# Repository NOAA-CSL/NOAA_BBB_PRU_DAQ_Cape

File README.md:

# NOAA BeagleBone Black (BBB) PRU DAQ Cape

<p>The NOAA BeagleBone Black PRU and DAQ Cape was developed for the NOAA Printed Optical Particle 
Spectrometer (POPS) instrument that is used to make balloon and aircraft particle concentration measurements. The 
POPS instrument is patented and can be licensed for $500 per year.  Contact Derek Parks (Derek.Parks@NOAA.gov) for 
more information. This cape and software has been patented and is being presented (with the included disclaimer) 
free for public download, modification and use. The programs that are presented are for the POPS instrument, and are
meant as an example and guide for developing other applications.

Cape Features
-----------------

* A high-speed LVDT serial interface using a DS90C124 deserializer.  It connects via a SATA cable to an 
LT2203 16 bit A/D converter located on the photomultiplier (PMT) interface board, sampling at 4 MHz.
This uses both PRUs to implement, and the data is passed in memory.

* MAX5802 D/A converter providing two 12-bit analog out channels (0-5 V) used for controlling the 
instrument's flow rate and laser power (0-5 V).

* An on-board MS5607-02BA03 pressure/temperature sensor.

* A DS3231 hardware realtime clock and battery holder.

* MAX3223 RS232 interface for two UARTs. UART1 is duplicated in TTL.

* M24256 cape EEPROM.

Provided Information
------------------------

* This README.md.

* SOFTWARE DISCLAIMER.md:  This file is to be included with any code that is copied from this 
distribution and used in another application.

* NOAA_BBB_PRU_DAQ_Cape_Setup.md:  This file describes how to setup the BeagleBone Black to 
correctly configure it to work with the cape.

* NOAA_BBB_PRU_DAQ_Cape Pin Use.md:  The pins used by the cape, and other pin information, is 
presented in this document as a table.

Hardware
------------

* README.md file for the hardware.

* NOAA_BBB_PRU_DAQ_Cape, PMT interface board, and base plate Eagle PCB files.

* BOM as an Excel spreadsheet for the boards.

Software and Examples
-------------------------

* build and build_dt:  Scripts to build the *.c and *.p files provided.

* cape-bone-iio-00A0.dtbo:  The analog in device tree binary object file.

* clock_init.sh:  The clock initialization shell.

* iolib.c, iolib.h, iolib.o, libiofunc.a and MAKEFILE:  The library libio is used for digital IO in the software.
	
* NOAA *.dts and *.dtbo files:  Used to set the Analog In, GPIO, PRUs and UARTS pins.

* PRU0_ParData.p, PRU1_All.p and PRU1_All_dt.p: Assembly language programs for the POPS instrument.

* POPS_BBB.c:  The main program for the POPS instrument. Demonstrates the capacity of the cape.

* POPS_BBB.cfg:  The configuration file for the POPS instrument.

* rc.local:  File for startup of services on boot.

* rtc-ds1307.service:  Hardware realtime clock service setup.

* Software_install_1 and Software_install_2:  Scripts for installing the software on the 
Beaglebone Black.

Disclaimer
----------------------------------

This repository is a scientific product and is not official communication of the National Oceanic and Atmospheric 
Administration, or the United States Department of Commerce. All NOAA GitHub project code is provided on an ‘as is’ basis 
and the user assumes responsibility for its use. NOAA has relinquished control of the information and no longer has 
responsibility to protect the integrity, confidentiality, or availability of the information. Any claims against the Department 
of Commerce or Department of Commerce bureaus stemming from the use of this GitHub project will be governed by all applicable 
Federal law. Any reference to specific commercial products, processes, or services by service mark, trademark, manufacturer,
or otherwise, does not constitute or imply their endorsement, recommendation or favoring by the Department of Commerce. The 
Department of Commerce seal and logo, or the seal and logo of a DOC bureau, shall not be used in any manner to imply endorsement 
of any commercial product or activity by DOC or the United States Government.

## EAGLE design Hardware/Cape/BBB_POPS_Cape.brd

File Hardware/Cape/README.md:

Beagle Bone Black (BBB) POPS Cape Notes
=======================================

<p>This cape is intended to be a part of a stack of printed circuit boards that comprise 
of the POPS instrument.  As you might expect, the cape plugs into the BBB and has M-F 
pass through connectors.  As currently used, the cape then plugs into a ‘base plate’ that
has some signal conditioning, and the rest of the instrument attaches to the base plate.  
Some signals are passed via the usual P8-P9 connectors, while other signals are passed to
the base plate via JP1, a 14 pin connector of similar style as P8 and P9.  If a base 
plate is not to be used, these signals are broken out on other connectors.

Note: The BeagelBone Black is mounted upside down on the base plate.

<p>The cape is powered by a signal labeled ‘V-Batt’.  This comes in via J1 pins 3 and 4,
or if a baseplate is not used, via the connector named ‘BATTERY_IN’.  This voltage is 
scaled and monitored via A/D channel AI6 pin P9.35.  To turn on the cape (which powers 
the BBB) the ‘ON’ button is pressed.  There is an ON button located on the cape, and can 
also have one on the baseplate using pin 12 of JP1.  The ON button turns on FET T3 which 
supplies +12V to the cape and to the base plate via J1 pins 5 and 6.  On the cape is a 5V 
regulator which then supplies +5V to the BBB via P9 pins P9.5 and P9.6.  The BBB then 
regulates the 5V down to +3.3V and supplies it back to the cape  via pins P9.3 and P9.4.  
Among other things, this 3.3V is then used to hold on FET T3 so the system remains powered 
up after the ON button is released.  When the BBB shuts down, 3.3V is removed from P9 and 
if the ON button is not pressed, power is removed from the rest of the system.

POPS Cape top view.

POPS Cape bottom view.

One of the functions of the cape is to read a differential pressure signal, compare against a setpoint (set by one of the two D/A channels) and control a small pump to maintain the setpoint.  The flow signal is the difference in pressure between the two ports on a laminar flow element.  This sub-system provides for a constant volume of gas flow.  The pump power is supplied via JP1 pins 1 and 2.  If a base plate is not used, connector P6 can be used.
The flow signal from the differential pressure sensor is supplied to the cape either via JP1 pin 13 or if the baseplate is not used, via J4.  It is scaled (conditioned) and is presented to the BBB via AIN0 P9.39.
Two 10K thermistors are measured on the POPS instrument.  One is external to the instrument connected to a connector on the base plate.  This in turn connects to the cape via JP1 pins 9 and 11.  This signal is scaled and provided to the BBB via AIN5 on P9.36.  The other thermistor monitors the laser diode temperature and connects to the POPS optical chamber via 5 pin P1 (note: not JP1!) pins 4 and 5.  Scaled signal is provided to the BBB via AIN2 on P9.367.  On both thermistors, one end is connected to a 3.6019V reference voltage and the other end connects to a 1.24K resistor to ground.  1.24K is also the resistance of the thermistor at its maximum expected temperature of 80.24 deg. C, which presents 1.8V to the BBB.  At 25 deg. C the thermistor value is 10K which presents 0.728V to the BBB.
The last signal on JP1 is named ‘PUSH_2_STOP’.  There is a button on the cape and can have a button on the baseplate.  This signal is buffered and presented to the BBB via P8.30.  It is monitored by the software and when asserted, (list the steps the software does, such as turn off laser, pump, stop taking data, close the files, run the shutdown sequence which removes the +3.3V signal from T3 and removes power to the BBB and cape).

Analog In Scale Factors.

AI0: Flow Signal.  5.036V from diff. pressure signal presents 1.8V to the BBB.
AI1: Pump Feedback.  15.000V from pump control circuit presents 1.8V to BBB.
AI2: Laser Temperature (10K Thermistor).  Max temperature is 80.24 deg. C which presents 1.8V to BBB.  25 deg. C presents 0.728V to BBB.
AI3: Laser Feedback. 5.036V from laser driver presents 1.8V to BBB.
AI4: Laser Photodiode Monitor. 5.036V from laser driver presents 1.8V to BBB.
AI5: External 10K Thermistor.  Max temperature is 80.24 deg. C which presents 1.8V to BBB.  25 deg. C presents 0.728V to BBB.
AI6: Battery Voltage. 20.119V input presents 1.8V to the BBB.

U1: I2C M24256 EEPROM. 

On this cape is a typical EEPROM which is not currently used with our software.  Solder jumpers SJ3 and SJ4 select the address.  By default (no solder jumpers) the address is 0x57.  0x54, 0x55, and 0x56 are the other options.  When SJ5 is shorted with a solder blob it write protects the EEPROM.  It is not write protected by default.  The SDA line is connected to P9.20 and the SCL line is connected to P9.19.

U2: I2C DS3231MZ/V Real Time Clock.

On this cape is a DS3231 battery backed up Real Time Clock.  This particular device has it’s own internal temperature compensated oscillator which keeps it accurate to +/- 5ppm (+/- 0.432 seconds per day) over it’s temperature range.  It’s fixed address is 0x68.  The SDA line is connected to P9.20 and the SCL line is connected to P9.19.  Backup power is provided by a BR1225 coin cell permanently soldered to the cape.  Not using a battery holder insures the coin cell won’t be jarred free.

U3: I2C MAX5802 12 bit dual D/A converter.

On this cape is a MAX5802 12 bit dual D/A converter.  It’s address is set to 0x0F by default and can be changed to 0x0C by moving solder jumper JMP7 to Vcc, or 0x0E by not connecting the solder jumper to either pad.  It is pin selected to have both outputs at 0V on power up and software selected max output voltage of 4.096V.  Ch. 1 controls the laser current and has a 0 to 100mA range.  The laser diode is rated for 100 mA continuous.  Out Ch. 2 provides the set point for the flow controller.  The controller servos the voltage to the pump so that this set point matches the signal from the flow sensor.  Since the actual flow signal is dependent on the laminar flow element geometries and particular differential pressure sensor used, the final calibration is done for each individual instrument.  Typical values have been around 3.5V from the D/A equal to 3 cc/second.

PRES1: SPI MS5607-02BA03 Barometric Pressure sensor with Temperature.

The MS5607 Barometric pressure sensor is used to measure altitude of the POPS instrument.  It has a range of 10 to 1200 mbar and a resolution of 0.024 mbar (20 cm of altitude).  Included is a 0.01 deg. C resolution, +/- 0.8 deg. C. accurate temperature sensor 
which is used to monitor the cape’s temperature.  The BBB talks to it via a bit-banged SPI interface with the SCLK to P9.13, the chip select signal connected to P9.14, the SDO to P9.15 and SDI to P9.16.

Serial Ports: RS-232 and TTL

There are two serial ports brought out on this cape.  UART1 TX signal (data leaving the cape) is on pin 9.24 and RX signal (data entering the cape) is on pin 9.26.  UART2 TX signal is on pin 9.21 and RX signal is on pin 9.22.  UART1 has two connectors.  J5 has the 3.3V TTL signals on it and J2 has the same data but buffered for RS-232 signal levels.  As for the UART1 RX signal, there is a solder jumper JMP2 that selects between the signal from the RS-232 buffer chip IC6 (MAX3223) or the signal from J5.  Since for our current applications no data is received on UART1 we currently don’t populate either side of solder jumper JMP2.  There is a through hole jumper connector that serves the same function as JMP2 called JP2.  If we had to frequently change which source of data JP2 would allow this without use of a soldering iron.  UART1 is used to send status data to either aircraft telemetry (the RS-232 buffered signal) or send 3.3V level status data to an IMET radiosonde via J5.  UART2 is always buffered to RS-232 signal levels and is on connector J3.  UART2 is used to communicate with a laptop running LabVIEW user interface software.

P2: High Speed A/D connector

In order to reduce interference and noise pickup, the high speed A/D converter is located as close to the signal source (Photo Multiplier Tube) as possible.  This converter is a Linear Technology LTC2203 16 bit, 25 MSPS converter with a parallel output, running at 4 MSPS.  The digital signals from the converter are serialized using a TI DS90C241 serializer.  The LVDS serial stream uses standard SATA connectors and cables to connect to the cape.  SATA cables were used for their low cost and availability.  Connector P2 on this cape has the serial data stream and provides power to the PMT and signal conditioning electronics.  The signals transferred are listed below.
Over/Underflow: P8.29
Data Ready: P8.27
AD15: P9.25
AD14: P9.41
AD13: P9.27
AD12: P9.42
AD11: P9.28
AD10: P9.30
AD9: P9.29
AD8: P9.31
AD7: P8.40
AD6:P9.39
AD5: P8.42
AD4: P8.41
AD3: P8.44
AD2: P8.43
AD1: P8.46
AD0: P8.45

There are 2 LEDs associated with the deserializer.  One to display the Over/Underflow status and another to show the status of the link between the deserializer and serializer.

P1: Laser connector

Connector P1 has 5 pins and connects to the laser inside the optical chamber.  Pin 1 is the laser diode Anode, pin 2 is the laser diode Cathode, and Pin 3 is the photodiode internal to the laser module.  0 to 100mA of current is controlled by the value on D/A channel A and the signal on pin 3 is signal conditioned and reported back to the BBB on channel AIN4.  Pin 4 has the reference voltage for the thermistor that is mounted on the laser’s heat sink, and pin 5 connects to ground through a 1.24K resistor.  The voltage on pin 5 is conditioned and sent to the BBB on channel AIN2.

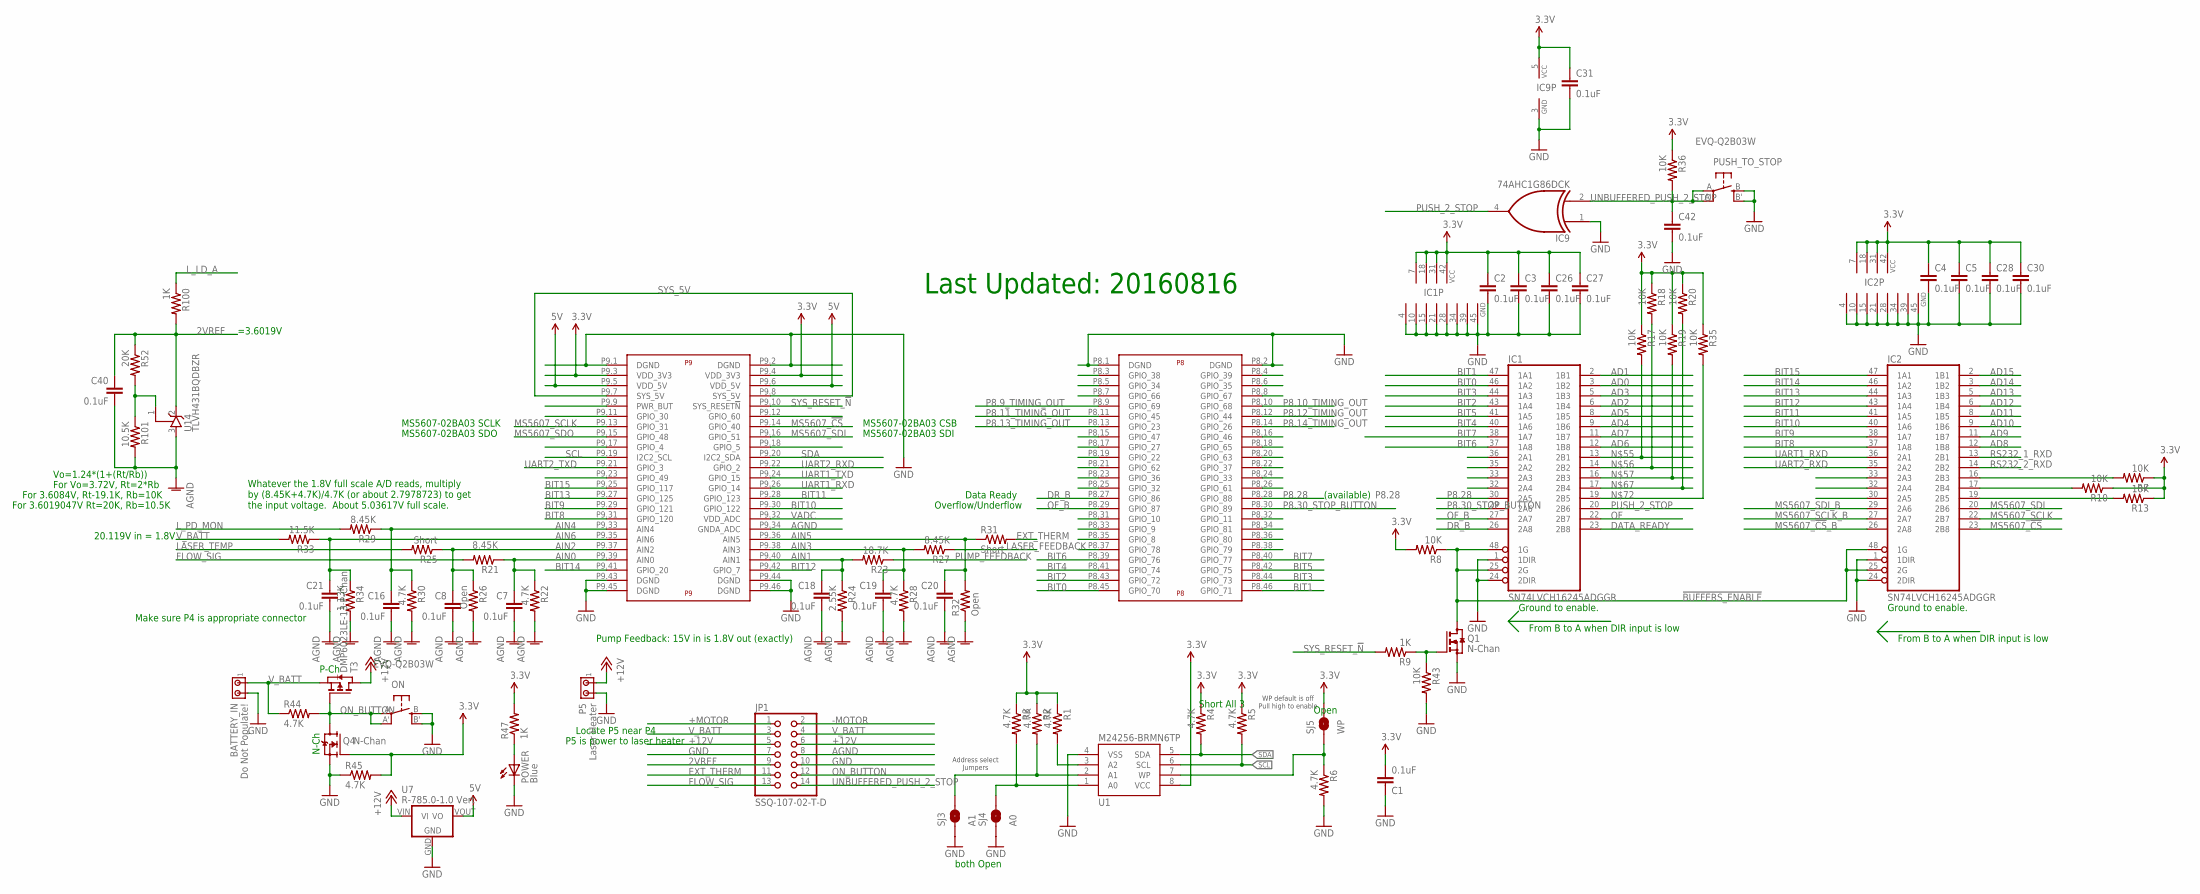
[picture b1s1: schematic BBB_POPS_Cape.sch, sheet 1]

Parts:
BATTERY_IN: Do Not Populate!; 070543-0036
C1, C2, C3, C4, C5, C7, C8, C16, C18, C19, C20, C21, C26, C27, C28, C30, C31, C40, C42: 0.1uF; 0603
IC1, IC2: SN74LVCH16245ADGGR; TSSOP-48
IC9: 74AHC1G86DCK; SC70-5
JP1: SSQ-107-02-T-D; 2X07_ROUND
ON: EVQ-Q2B03W; EVQ-Q2
P5: Laser Heater; 501568-0207_2-PIN
POWER: Blue; LED-805
PUSH_TO_STOP: EVQ-Q2B03W; EVQ-Q2
Q1: N-Chan; SOT23
Q4: N-Chan; SOT-23
R1, R2, R3, R4, R5, R6, R22, R28, R30, R44, R45: 4.7K; 0603
R7, R8, R10, R13, R17, R18, R19, R20, R35, R36, R43: 10K; 0603
R9, R47, R100: 1K; 0603
R21, R27, R29: 8.45K; 0603
R23: 18.7K; 0603
R24: 2.55K; 0603
R25, R31: Short; 0603
R26, R32: Open; 0603
R33: 11.5K; 0603
R34: 1.13K; 0603
R52: 20K; 0603
R101: 10.5K; 0603
SJ3: A1; SJ_2S-NO
SJ4: A0; SJ_2S-NO
SJ5: WP; SJ_2S-NO
T3: DMP6023LE-13 P-Chan; SOT223
U1: M24256-BRMN6TP; SO08
U7: R-785.0-1.0 Vert; RECOM_R-78X-1.0
U14: TLVH431BQDBZR; SOT23
U$2: BEAGLE_BONE_BLACK_CAPEME; MY_BBB_CAPE

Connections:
2VREF: C40.1, JP1.9, R52.1, R100.2, U14.2 (C); also elsewhere on the board
3.3V: C1.2, C2.1, C3.1, C4.1, C5.1, C26.1, C27.1, C28.1, C30.1, C31.1, IC1.7 (VCC), IC1.18 (VCC), IC1.31 (VCC), IC1.42 (VCC), IC2.7 (VCC), IC2.18 (VCC), IC2.31 (VCC), IC2.42 (VCC), IC9.5 (VCC), Q4.1 (G), R1.1, R2.1, R3.1, R4.1, R5.1, R7.1, R8.2, R10.1, R13.1, R17.1, R18.1, R19.1, R20.1, R35.1, R36.1, R45.2, R47.2, SJ5.2, U1.8 (VCC), U$2.P9.3 (VDD_3V3), U$2.P9.4 (VDD_3V3); also elsewhere on the board
5V: U7.VOUT (VO), U$2.P9.5 (VDD_5V), U$2.P9.6 (VDD_5V); also elsewhere on the board
!BUFFERS_ENABLE: IC1.25 (2G), IC1.48 (1G), IC2.25 (2G), IC2.48 (1G), Q1.3 (D), R8.1
+12V: JP1.5, JP1.6, P5.1, T3.2 (D), T3.4 (D), U7.VIN (VI); also elsewhere on the board
+MOTOR: JP1.1; also elsewhere on the board
-MOTOR: JP1.2; also elsewhere on the board
A0: R3.2, SJ4.2, U1.1 (A0)
A1: R2.2, SJ3.2, U1.2 (A1)
AD0: IC1.3 (1B2); also elsewhere on the board
AD1: IC1.2 (1B1); also elsewhere on the board
AD2: IC1.6 (1B4); also elsewhere on the board
AD3: IC1.5 (1B3); also elsewhere on the board
AD4: IC1.9 (1B6); also elsewhere on the board
AD5: IC1.8 (1B5); also elsewhere on the board
AD6: IC1.12 (1B8); also elsewhere on the board
AD7: IC1.11 (1B7); also elsewhere on the board
AD8: IC2.12 (1B8); also elsewhere on the board
AD9: IC2.11 (1B7); also elsewhere on the board
AD10: IC2.9 (1B6); also elsewhere on the board
AD11: IC2.8 (1B5); also elsewhere on the board
AD12: IC2.6 (1B4); also elsewhere on the board
AD13: IC2.5 (1B3); also elsewhere on the board
AD14: IC2.3 (1B2); also elsewhere on the board
AD15: IC2.2 (1B1); also elsewhere on the board
AGND: C7.2, C8.2, C16.2, C18.2, C19.2, C20.2, C21.2, C40.2, JP1.8, R22.2, R24.2, R26.2, R28.2, R30.2, R32.1, R34.2, R101.2, U14.3 (A), U$2.P9.34 (GNDA_ADC); also elsewhere on the board
AIN0: C7.1, R21.1, R22.1, U$2.P9.39 (AIN0)
AIN1: C18.1, R23.2, R24.1, U$2.P9.40 (AIN1)
AIN2: C8.1, R25.1, R26.1, U$2.P9.37 (AIN2)
AIN3: C19.1, R27.2, R28.1, U$2.P9.38 (AIN3)
AIN4: C16.1, R29.1, R30.1, U$2.P9.33 (AIN4)
AIN5: C20.1, R31.1, R32.2, U$2.P9.36 (AIN5)
AIN6: C21.1, R33.1, R34.1, U$2.P9.35 (AIN6)
BIT0: IC1.46 (1A2), U$2.P8.45 (GPIO_70)
BIT1: IC1.47 (1A1), U$2.P8.46 (GPIO_71)
BIT2: IC1.43 (1A4), U$2.P8.43 (GPIO_72)
BIT3: IC1.44 (1A3), U$2.P8.44 (GPIO_73)
BIT4: IC1.40 (1A6), U$2.P8.41 (GPIO_74)
BIT5: IC1.41 (1A5), U$2.P8.42 (GPIO_75)
BIT6: IC1.37 (1A8), U$2.P8.39 (GPIO_76)
BIT7: IC1.38 (1A7), U$2.P8.40 (GPIO_77)
BIT8: IC2.37 (1A8), U$2.P9.31 (GPIO_120)
BIT9: IC2.38 (1A7), U$2.P9.29 (GPIO_121)
BIT10: IC2.40 (1A6), U$2.P9.30 (GPIO_122)
BIT11: IC2.41 (1A5), U$2.P9.28 (GPIO_123)
BIT12: IC2.43 (1A4), U$2.P9.42 (GPIO_7)
BIT13: IC2.44 (1A3), U$2.P9.27 (GPIO_125)
BIT14: IC2.46 (1A2), U$2.P9.41 (GPIO_20)
BIT15: IC2.47 (1A1), U$2.P9.25 (GPIO_117)
DATA_READY: IC1.23 (2B8); also elsewhere on the board
DR_B: IC1.26 (2A8), U$2.P8.27 (GPIO_86)
EXT_THERM: JP1.11, R31.2; also elsewhere on the board
FLOW_SIG: JP1.13, R21.2; also elsewhere on the board
GND: BATTERY_IN.P$2 (2), C1.1, C2.2, C3.2, C4.2, C5.2, C26.2, C27.2, C28.2, C30.2, C31.2, C42.2, IC1.1 (1DIR), IC1.4 (GND), IC1.10 (GND), IC1.15 (GND), IC1.21 (GND), IC1.24 (2DIR), IC1.28 (GND), IC1.34 (GND), IC1.39 (GND), IC1.45 (GND), IC2.1 (1DIR), IC2.4 (GND), IC2.10 (GND), IC2.15 (GND), IC2.21 (GND), IC2.24 (2DIR), IC2.28 (GND), IC2.34 (GND), IC2.39 (GND), IC2.45 (GND), IC9.1 (I0), IC9.3 (GND), JP1.7, JP1.10, ON.B (S), ON.B' (S1), P5.2, POWER.C, PUSH_TO_STOP.B (S), PUSH_TO_STOP.B' (S1), Q1.2 (S), Q4.2 (S), R6.2, R43.2, R45.1, SJ3.1, SJ4.1, U1.4 (VSS), U7.GND, U$2.P8.1 (DGND), U$2.P8.2 (DGND), U$2.P9.1 (DGND), U$2.P9.2 (DGND), U$2.P9.43 (DGND), U$2.P9.44 (DGND), U$2.P9.45 (DGND), U$2.P9.46 (DGND); also elsewhere on the board
LASER_FEEDBACK: R27.1; also elsewhere on the board
LASER_TEMP: R25.2; also elsewhere on the board
L_LD_A: R100.1; also elsewhere on the board
L_PD_MON: R29.2; also elsewhere on the board
MS5607_!CS: IC2.23 (2B8), U$2.P9.14 (GPIO_40)
MS5607_!CS!_B: IC2.26 (2A8); also elsewhere on the board
MS5607_SCLK: IC2.22 (2B7), U$2.P9.13 (GPIO_31)
MS5607_SCLK_B: IC2.27 (2A7); also elsewhere on the board
MS5607_SDI: IC2.20 (2B6), U$2.P9.16 (GPIO_51)
MS5607_SDI_B: IC2.29 (2A6); also elsewhere on the board
MS5607_SDO: U$2.P9.15 (GPIO_48); also elsewhere on the board
unnamed: R6.1, SJ5.1, U1.7 (WP)
unnamed: Q1.1 (G), R9.1, R43.1
unnamed: IC2.16 (2B3), R7.2
unnamed: R1.2, U1.3 (A2)
unnamed: R52.2, R101.1, U14.1 (R)
unnamed: IC2.17 (2B4), R10.2
unnamed: IC2.19 (2B5), R13.2
unnamed: IC1.13 (2B1), R17.2
unnamed: IC1.14 (2B2), R18.2
unnamed: IC1.16 (2B3), R19.2
unnamed: IC1.17 (2B4), R20.2
unnamed: IC1.19 (2B5), R35.2
unnamed: POWER.A, R47.1
OF: IC1.22 (2B7); also elsewhere on the board
OF_B: IC1.27 (2A7), U$2.P8.29 (GPIO_87)
ON_BUTTON: JP1.12, ON.A, ON.A' (P1), Q4.3 (D), R44.2, T3.1 (G)
P8.9_TIMING_OUT: U$2.P8.9 (GPIO_69)
P8.10_TIMING_OUT: U$2.P8.10 (GPIO_68)
P8.11_TIMING_OUT: U$2.P8.11 (GPIO_45)
P8.12_TIMING_OUT: U$2.P8.12 (GPIO_44)
P8.13_TIMING_OUT: U$2.P8.13 (GPIO_23)
P8.14_TIMING_OUT: U$2.P8.14 (GPIO_26)
P8.28: IC1.30 (2A5), U$2.P8.28 (GPIO_88)
P8.30_STOP_BUTTON: IC1.29 (2A6), U$2.P8.30 (GPIO_89)
PUMP_FEEDBACK: R23.1; also elsewhere on the board
PUSH_2_STOP: IC1.20 (2B6), IC9.4 (O)
RS232_1_RXD: IC2.13 (2B1); also elsewhere on the board
RS232_2_RXD: IC2.14 (2B2); also elsewhere on the board
SCL: R5.2, U1.6 (SCL), U$2.P9.19 (I2C2_SCL); also elsewhere on the board
SDA: R4.2, U1.5 (SDA), U$2.P9.20 (I2C2_SDA); also elsewhere on the board
SYS_5V: U$2.P9.7 (SYS_5V), U$2.P9.8 (SYS_5V)
SYS_RESET_!N: R9.2, U$2.P9.10 (SYS_RESET!N)
UART1_RXD: IC2.36 (2A1), U$2.P9.26 (GPIO_14)
UART1_TXD: U$2.P9.24 (GPIO_15); also elsewhere on the board
UART2_RXD: IC2.35 (2A2), U$2.P9.22 (GPIO_2)
UART2_TXD: U$2.P9.21 (GPIO_3); also elsewhere on the board
UNBUFFERED_PUSH_2_STOP: C42.1, IC9.2 (I1), JP1.14, PUSH_TO_STOP.A, PUSH_TO_STOP.A' (P1), R36.2
VADC: U$2.P9.32 (VDD_ADC)
V_BATT: BATTERY_IN.P$1 (1), JP1.3, JP1.4, R33.2, R44.1, T3.3 (S)

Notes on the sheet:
WP default is off Pull high to enable
Address select Jumpers
Ground to enable.
(available)
Data Ready
Overflow/Underflow
Last Updated: 20160816
Open
both Open
Short All 3
Whatever the 1.8V full scale A/D reads, multiply by (8.45K+4.7K)/4.7K (or about 2.7978723) to get the input voltage. About 5.03617V full scale.
MS5607-02BA03 CSB
MS5607-02BA03 SCLK
MS5607-02BA03 SDO
MS5607-02BA03 SDI
Make sure P4 is appropriate connector
20.119V in = 1.8V
P5 is power to laser heater
Locate P5 near P4
From B to A when DIR input is low
Vo=1.24*(1+(Rt/Rb))
For Vo=3.72V, Rt=2*Rb
N-Ch
P-Ch
For 3.6084V, Rt-19.1K, Rb=10K
=3.6019V
For 3.6019047V Rt=20K, Rb=10.5K
Pump Feedback: 15V in is 1.8V out (exactly)

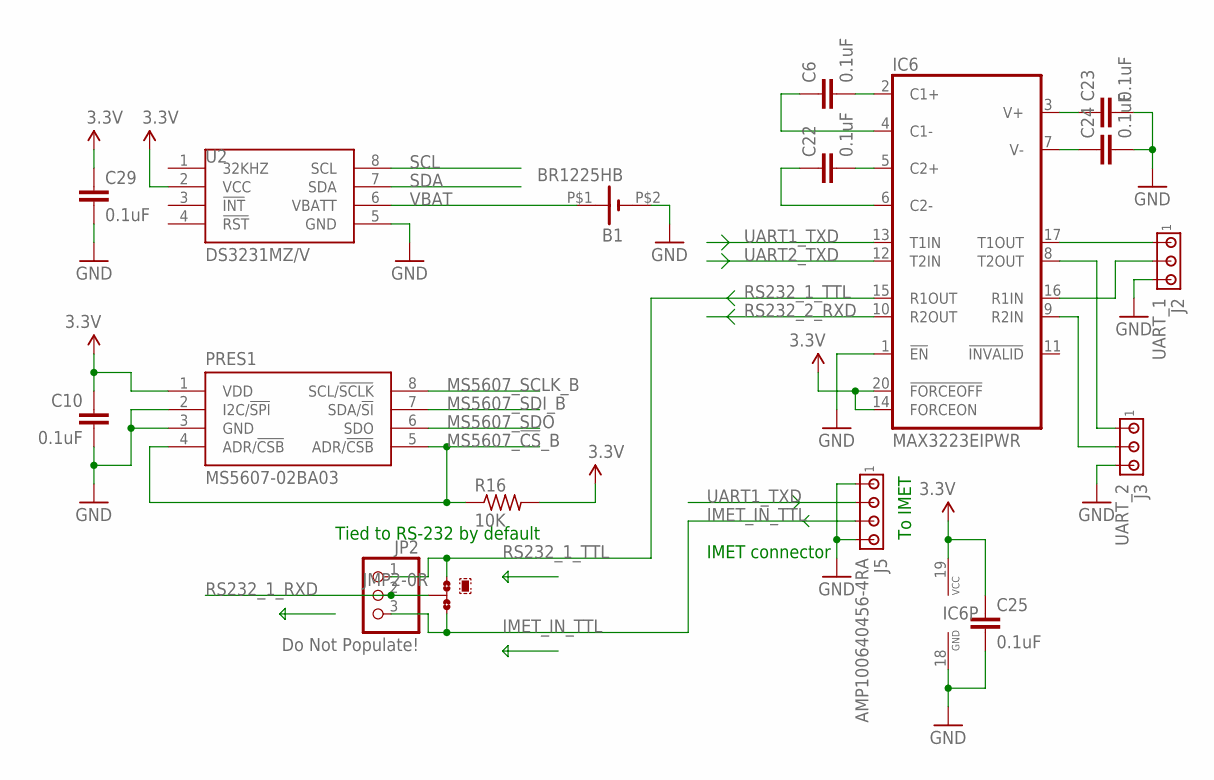
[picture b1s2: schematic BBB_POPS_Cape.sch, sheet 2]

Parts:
B1: BR1225HB; BR1225A/HB
C6, C10, C22, C23, C24, C25, C29: 0.1uF; 0603
IC6: MAX3223EIPWR; TSSOP20
J2: UART_1; 640457-3
J3: UART_2; 640457-3
J5: AMP100640456-4RA; 640457-4
JMP2: 0R-JUMPMINE; MY_C0R-JMP
JP2: Do Not Populate!; 1X03_ROUND
PRES1: MS5607-02BA03; MS5607-02BA
R16: 10K; 0603
U2: DS3231MZ/V; SO08

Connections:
3.3V: C10.1, C25.1, C29.1, IC6.14 (FORCEON), IC6.19 (VCC), IC6.20 (!FORCEOFF), PRES1.1 (VDD), R16.2, U2.2 (VCC); also elsewhere on the board
GND: B1.P$2 (-), C10.2, C23.2, C24.2, C25.2, C29.2, IC6.1 (!EN), IC6.18 (GND), J2.3, J3.3, J5.1, J5.4, PRES1.2 (I2C/!SPI), PRES1.3 (GND), U2.5 (GND); also elsewhere on the board
IMET_IN_TTL: J5.3, JMP2.3, JP2.3
MS5607_!CS!_B: PRES1.4 (ADR/!CSB), PRES1.5 (ADR/!CSB), R16.1; also elsewhere on the board
MS5607_SCLK_B: PRES1.8 (SCL/!SCLK); also elsewhere on the board
MS5607_SDI_B: PRES1.7 (SDA/!SI); also elsewhere on the board
MS5607_SDO: PRES1.6 (SDO); also elsewhere on the board
unnamed: IC6.16 (R1IN), J2.2
unnamed: IC6.8 (T2OUT), J3.1
unnamed: IC6.9 (R2IN), J3.2
unnamed: IC6.17 (T1OUT), J2.1
unnamed: C6.2, IC6.2 (C1+)
unnamed: C22.2, IC6.5 (C2+)
unnamed: C23.1, IC6.3 (V+)
unnamed: C24.1, IC6.7 (V-)
unnamed: C6.1, IC6.4 (C1-)
unnamed: C22.1, IC6.6 (C2-)
RS232_1_RXD: JMP2.2, JP2.2; also elsewhere on the board
RS232_1_TTL: IC6.15 (R1OUT), JMP2.1, JP2.1
RS232_2_RXD: IC6.10 (R2OUT); also elsewhere on the board
SCL: U2.8 (SCL); also elsewhere on the board
SDA: U2.7 (SDA); also elsewhere on the board
UART1_TXD: IC6.13 (T1IN), J5.2; also elsewhere on the board
UART2_TXD: IC6.12 (T2IN); also elsewhere on the board
VBAT: B1.P$1 (+), U2.6 (VBATT)

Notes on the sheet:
IMET connector
To IMET
Tied to RS-232 by default

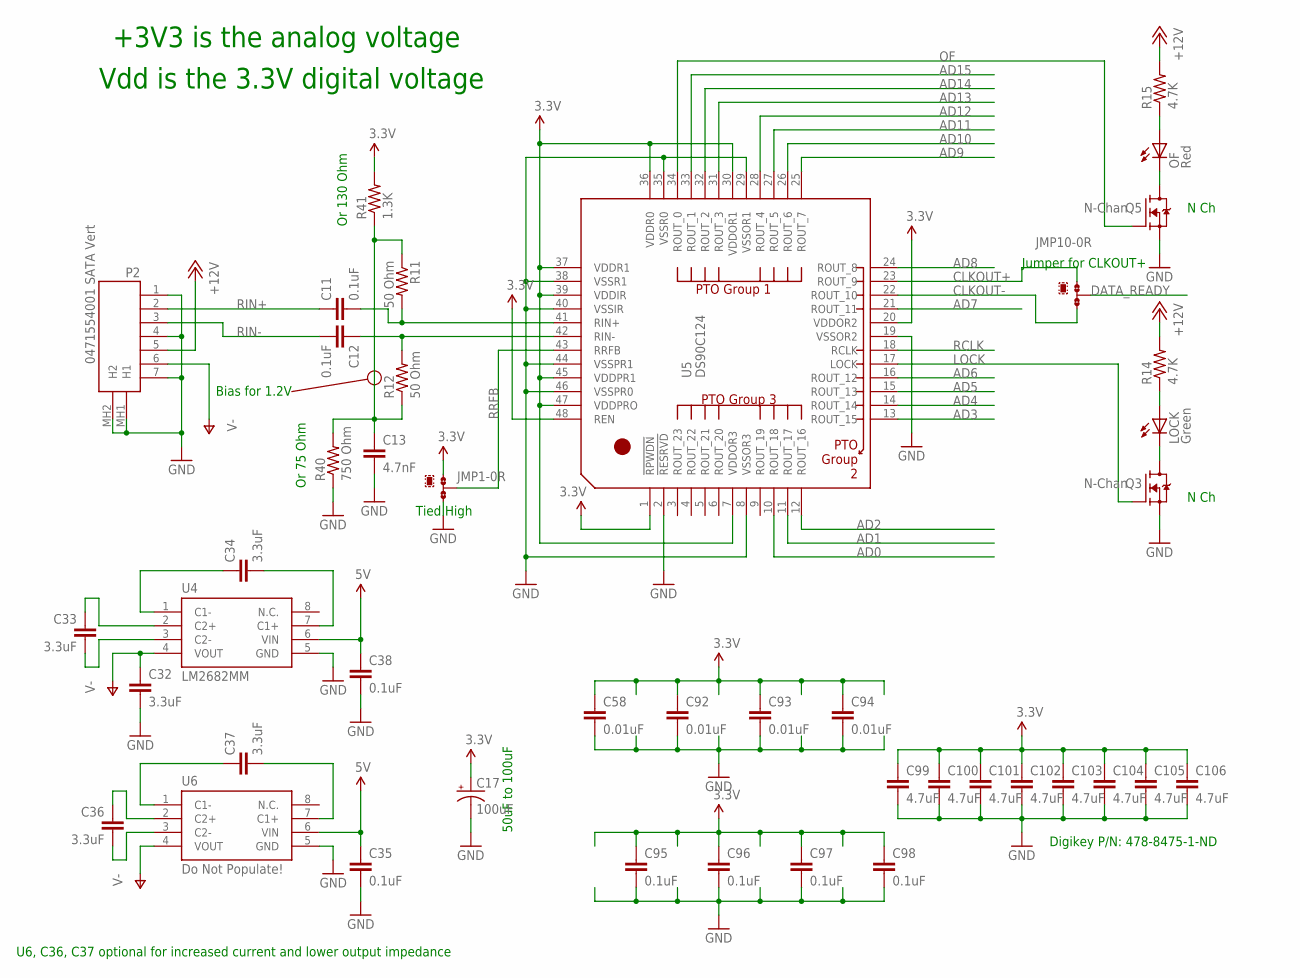
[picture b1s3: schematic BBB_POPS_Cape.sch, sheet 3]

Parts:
C11, C12, C35, C38, C95, C96, C97, C98: 0.1uF; 0603
C13: 4.7nF; 0805_MARISS
C17: 100uF; C/6032-28R
C32, C33, C34, C36, C37: 3.3uF; 0805_MARISS
C58, C92, C93, C94: 0.01uF; 0603
C99, C100, C101, C102, C103, C104, C105, C106: 4.7uF; 0805_MARISS
JMP1, JMP10: 0R-JUMPMINE; MY_C0R-JMP
LOCK: Green; LED-805
OF: Red; LED-805
P2: 0471554001 SATA Vert; 0471554001
Q3, Q5: N-Chan; SOT-23
R11, R12: 50 Ohm; 0603
R14, R15: 4.7K; 0603
R40: 750 Ohm; 0603
R41: 1.3K; 0603
U4: LM2682MM; MY_DGK_S-PDSO-G8
U5: DS90C124; PFB_S-PQFP-G48
U6: Do Not Populate!; MY_DGK_S-PDSO-G8

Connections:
1.2V_BIAS1: C13.1, R11.1, R12.1, R40.2, R41.1
3.3V: C17.+, C58.1, C92.1, C93.1, C94.1, C95.1, C96.1, C97.1, C98.1, C99.1, C100.1, C101.1, C102.1, C103.1, C104.1, C105.1, C106.1, JMP1.1, R41.2, U5.1 (!RPWDN), U5.7 (VDDOR3), U5.20 (VDDOR2), U5.30 (VDDOR1), U5.36 (VDDR0), U5.37 (VDDR1), U5.39 (VDDIR), U5.45 (VDDPR1), U5.47 (VDDPRO), U5.48 (REN); also elsewhere on the board
5V: C35.1, C38.1, U4.6 (VIN), U6.6 (VIN); also elsewhere on the board
+12V: P2.5, R14.2, R15.2; also elsewhere on the board
AD0: U5.10 (ROUT_18); also elsewhere on the board
AD1: U5.11 (ROUT_17); also elsewhere on the board
AD2: U5.12 (ROUT_16); also elsewhere on the board
AD3: U5.13 (ROUT_15); also elsewhere on the board
AD4: U5.14 (ROUT_14); also elsewhere on the board
AD5: U5.15 (ROUT_13); also elsewhere on the board
AD6: U5.16 (ROUT_12); also elsewhere on the board
AD7: U5.21 (ROUT_11); also elsewhere on the board
AD8: U5.24 (ROUT_8); also elsewhere on the board
AD9: U5.25 (ROUT_7); also elsewhere on the board
AD10: U5.26 (ROUT_6); also elsewhere on the board
AD11: U5.27 (ROUT_5); also elsewhere on the board
AD12: U5.28 (ROUT_4); also elsewhere on the board
AD13: U5.31 (ROUT_3); also elsewhere on the board
AD14: U5.32 (ROUT_2); also elsewhere on the board
AD15: U5.33 (ROUT_1); also elsewhere on the board
CLKOUT+: JMP10.1, U5.23 (ROUT_9)
CLKOUT-: JMP10.3, U5.22 (ROUT_10)
DATA_READY: JMP10.2; also elsewhere on the board
GND: C13.2, C17.-, C32.2, C35.2, C38.2, C58.2, C92.2, C93.2, C94.2, C95.2, C96.2, C97.2, C98.2, C99.2, C100.2, C101.2, C102.2, C103.2, C104.2, C105.2, C106.2, JMP1.3, P2.1, P2.4, P2.7, P2.MH1 (H1), P2.MH2 (H2), Q3.2 (S), Q5.2 (S), R40.1, U4.5 (GND), U5.2 (!RESRVD), U5.8 (VSSOR3), U5.19 (VSSOR2), U5.29 (VSSOR1), U5.35 (VSSR0), U5.38 (VSSR1), U5.40 (VSSIR), U5.44 (VSSPR1), U5.46 (VSSPR0), U6.5 (GND); also elsewhere on the board
LOCK: Q3.1 (G), U5.17 (LOCK)
unnamed: C11.2, R11.2, U5.41 (RIN+)
unnamed: LOCK.C, Q3.3 (D)
unnamed: C12.1, R12.2, U5.42 (RIN-)
unnamed: OF.A, R15.1
unnamed: OF.C, Q5.3 (D)
unnamed: C37.1, U6.1 (C1-)
unnamed: C34.1, U4.1 (C1-)
unnamed: C34.2, U4.7 (C1+)
unnamed: C33.1, U4.2 (C2+)
unnamed: C33.2, U4.3 (C2-)
unnamed: C37.2, U6.7 (C1+)
unnamed: C36.1, U6.2 (C2+)
unnamed: C36.2, U6.3 (C2-)
unnamed: LOCK.A, R14.1
OF: Q5.1 (G), U5.34 (ROUT_0); also elsewhere on the board
RCLK: U5.18 (RCLK)
RIN+: C11.1, P2.2
RIN-: C12.2, P2.3
RRFB: JMP1.2, U5.43 (RRFB)
V-: C32.1, P2.6, U4.4 (VOUT), U6.4 (VOUT)

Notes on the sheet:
Or 75 Ohm
Or 130 Ohm
Bias for 1.2V
50uF to 100uF
Digikey P/N: 478-8475-1-ND
+3V3 is the analog voltage
Vdd is the 3.3V digital voltage
Jumper for CLKOUT+
U6, C36, C37 optional for increased current and lower output impedance
N Ch
Tied High

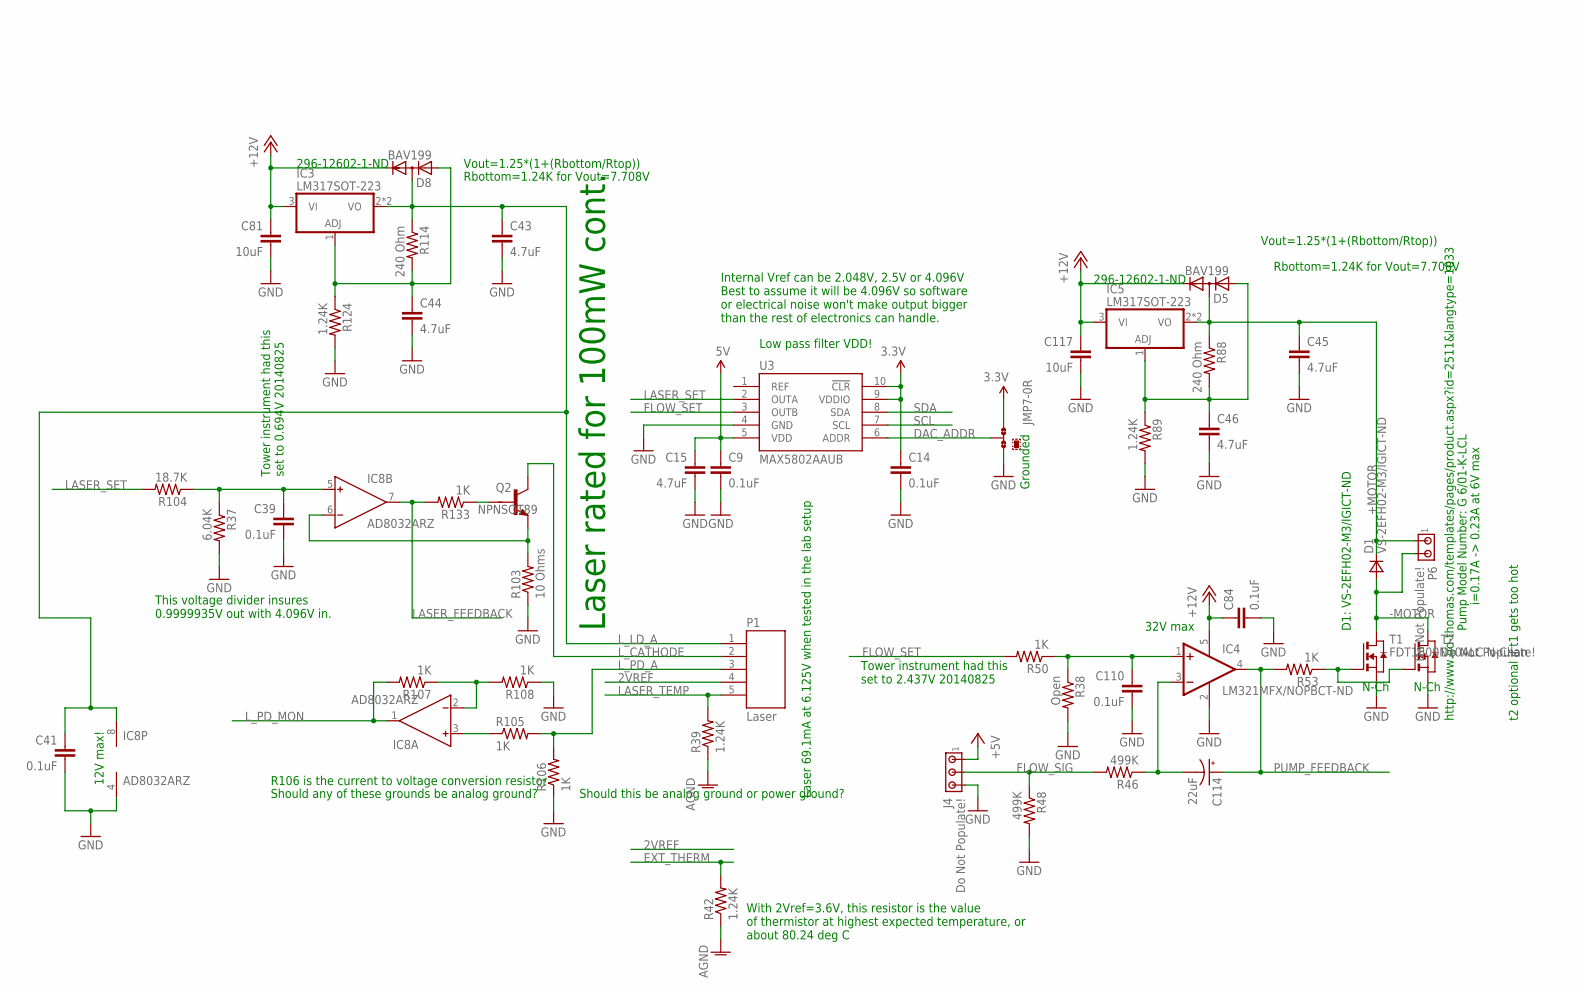
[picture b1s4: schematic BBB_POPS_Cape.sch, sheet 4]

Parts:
C9, C14, C39, C41, C84, C110: 0.1uF; 0603
C15, C43, C44, C45, C46: 4.7uF; 0805_MARISS
C81, C117: 10uF; 0805_MARISS
C114: 22uF; SMC_B
D1: VS-2EFH02-M3/IGICT-ND; DO-219ABVISHAY
D5, D8: BAV199; SOT23
IC3, IC5: LM317SOT-223; S0T-223
IC4: LM321MFX/NOPBCT-ND; SOT23-5
IC8: AD8032ARZ; SO8
J4: Do Not Populate!; 640457-3
JMP7: 0R-JUMPMINE; MY_C0R-JMP
P1: Laser; 501568-0509
P6: Do Not Populate!; 0705530001_2-PIN_H_CGRID_SL
Q2: NPNSOT89; SOT89
R37: 6.04K; 0603
R38: Open; 0603
R39, R42, R89, R124: 1.24K; 0603
R46, R48: 499K; 0603
R50, R53, R105, R106, R107, R108, R133: 1K; 0603
R88, R114: 240 Ohm; 0603
R103: 10 Ohms; R1206
R104: 18.7K; 0603
T1: FDT1600N10ALC N-Chan; SOT223
T2: Do Not Populate!; SOT223
U3: MAX5802AAUB; MY_UMAX10

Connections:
2VREF: P1.4; also elsewhere on the board
3.3V: C14.1, JMP7.1, U3.9 (VDDIO), U3.10 (!CLR); also elsewhere on the board
5V: C9.1, C15.1, U3.5 (VDD); also elsewhere on the board
+5V: J4.1
+12V: C81.1, C84.1, C117.1, D5.2 (C), D8.2 (C), IC3.3 (VI), IC4.5 (V+), IC5.3 (VI); also elsewhere on the board
+MOTOR: C45.1, D1.C, D5.3 (AC), IC5.2 (VO), IC5.4 (VO), P6.P$1 (1), R88.1; also elsewhere on the board
-MOTOR: D1.A, P6.P$2 (2), T1.2 (D), T1.4 (D), T2.2 (D), T2.4 (D); also elsewhere on the board
AGND: R39.1, R42.1; also elsewhere on the board
D/A_3: C110.1, IC4.1 (+IN), R38.1, R50.1
DAC_ADDR: JMP7.2, U3.6 (ADDR)
EXT_THERM: R42.2; also elsewhere on the board
FLOW_SET: R50.2, U3.3 (OUTB)
FLOW_SIG: J4.2, R46.2, R48.1; also elsewhere on the board
GND: C9.2, C14.2, C15.2, C39.2, C41.2, C43.2, C44.2, C45.2, C46.2, C81.2, C84.2, C110.2, C117.2, IC4.2 (V-), IC8.4 (V-), J4.3, JMP7.3, R37.2, R38.2, R48.2, R89.2, R103.1, R106.1, R108.1, R124.2, T1.3 (S), T2.3 (S), U3.4 (GND); also elsewhere on the board
LASER_FEEDBACK: IC8.7 (OUT), R133.2; also elsewhere on the board
LASER_SET: R104.2, U3.2 (OUTA)
LASER_TEMP: P1.5, R39.2; also elsewhere on the board
L_CATHODE: P1.2, Q2.2 (C1), Q2.2@1 (C1)
L_LD_A: C41.1, C43.1, D8.3 (AC), IC3.2 (VO), IC3.4 (VO), IC8.8 (V+), P1.1, R114.1; also elsewhere on the board
L_PD_A: P1.3, R105.2, R106.2
L_PD_MON: IC8.1 (OUT), R107.2; also elsewhere on the board
unnamed: Q2.1 (B1), R133.1
unnamed: R53.1, T1.1 (G), T2.1 (G)
unnamed: C46.1, D5.1 (A), IC5.1 (ADJ), R88.2, R89.1
unnamed: C114.-, IC4.3 (-IN), R46.1
unnamed: IC8.6 (IN-), Q2.3 (E1), R103.2
unnamed: C39.1, IC8.5 (IN+), R37.1, R104.1
unnamed: IC8.2 (IN-), R107.1, R108.2
unnamed: IC8.3 (IN+), R105.1
unnamed: C44.1, D8.1 (A), IC3.1 (ADJ), R114.2, R124.1
PUMP_FEEDBACK: C114.+, IC4.4 (OUT), R53.2; also elsewhere on the board
SCL: U3.7 (SCL); also elsewhere on the board
SDA: U3.8 (SDA); also elsewhere on the board

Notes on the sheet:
Laser 69.1mA at 6.125V when tested in the lab setup
R106 is the current to voltage conversion resistor
Vout=1.25*(1+(Rbottom/Rtop))
Rbottom=1.24K for Vout=7.708V
Tower instrument had this set to 2.437V 20140825
Tower instrument had this set to 0.694V 20140825
Grounded
Low pass filter VDD!
Laser rated for 100mW cont.
Internal Vref can be 2.048V, 2.5V or 4.096V Best to assume it will be 4.096V so software or electrical noise won't make output bigger than the rest of electronics can handle.
This voltage divider insures 0.9999935V out with 4.096V in.
http://www.gd-thomas.com/templates/pages/product.aspx?id=2511&langtype=1033
Pump Model Number: G 6/01-K-LCL
i=0.17A -> 0.23A at 6V max
296-12602-1-ND
Should any of these grounds be analog ground?
Should this be analog ground or power ground?
D1: VS-2EFH02-M3/IGICT-ND
t2 optional if t1 gets too hot
12V max!
32V max
N-Ch
With 2Vref=3.6V, this resistor is the value of thermistor at highest expected temperature, or about 80.24 deg C

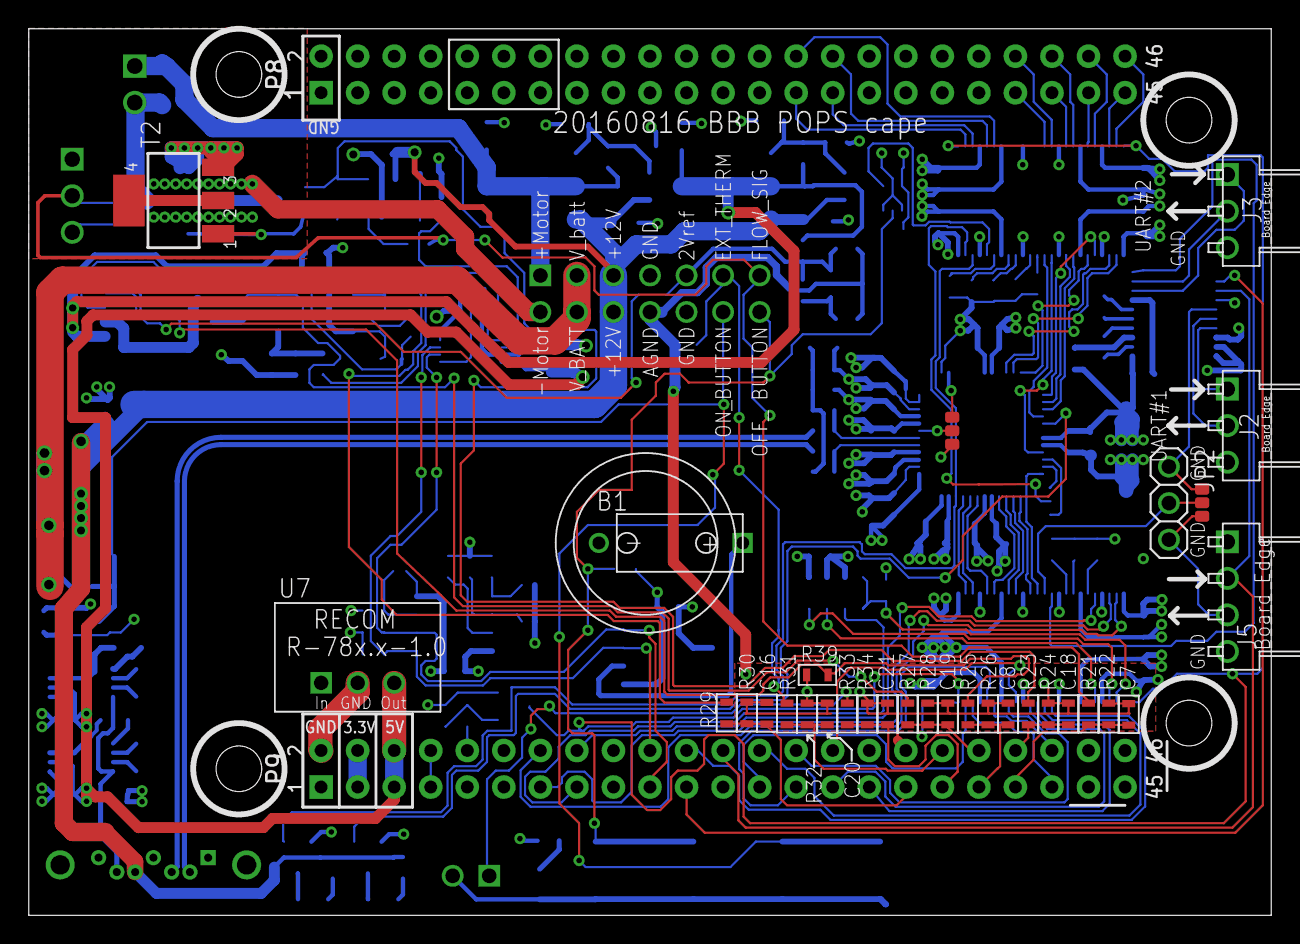
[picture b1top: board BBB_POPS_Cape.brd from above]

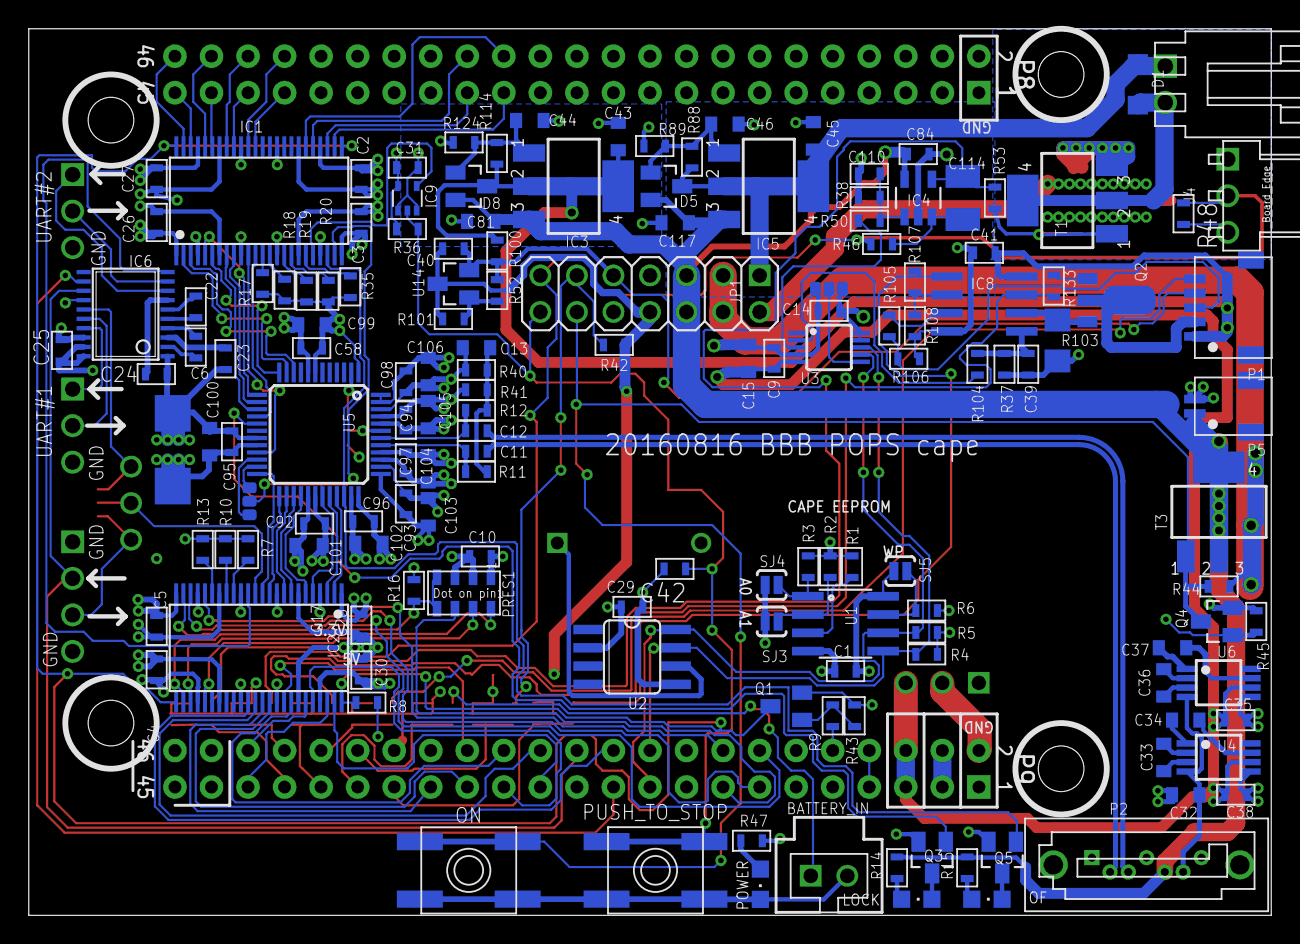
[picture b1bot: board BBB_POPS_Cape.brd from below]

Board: 4 copper layers, 86.4 x 61.6 mm, 184 parts (152 on the bottom side), 147 nets.

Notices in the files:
parts and their libraries:
SparkFun-DigitalIC: Licensing: CC v3.0 Share-Alike You are welcome to use this library for commercial purposes.
MySparkFun-Boards: Licensing: Creative Commons ShareAlike 4.0 International - https://creativecommons.org/licenses/by-sa/4.0
